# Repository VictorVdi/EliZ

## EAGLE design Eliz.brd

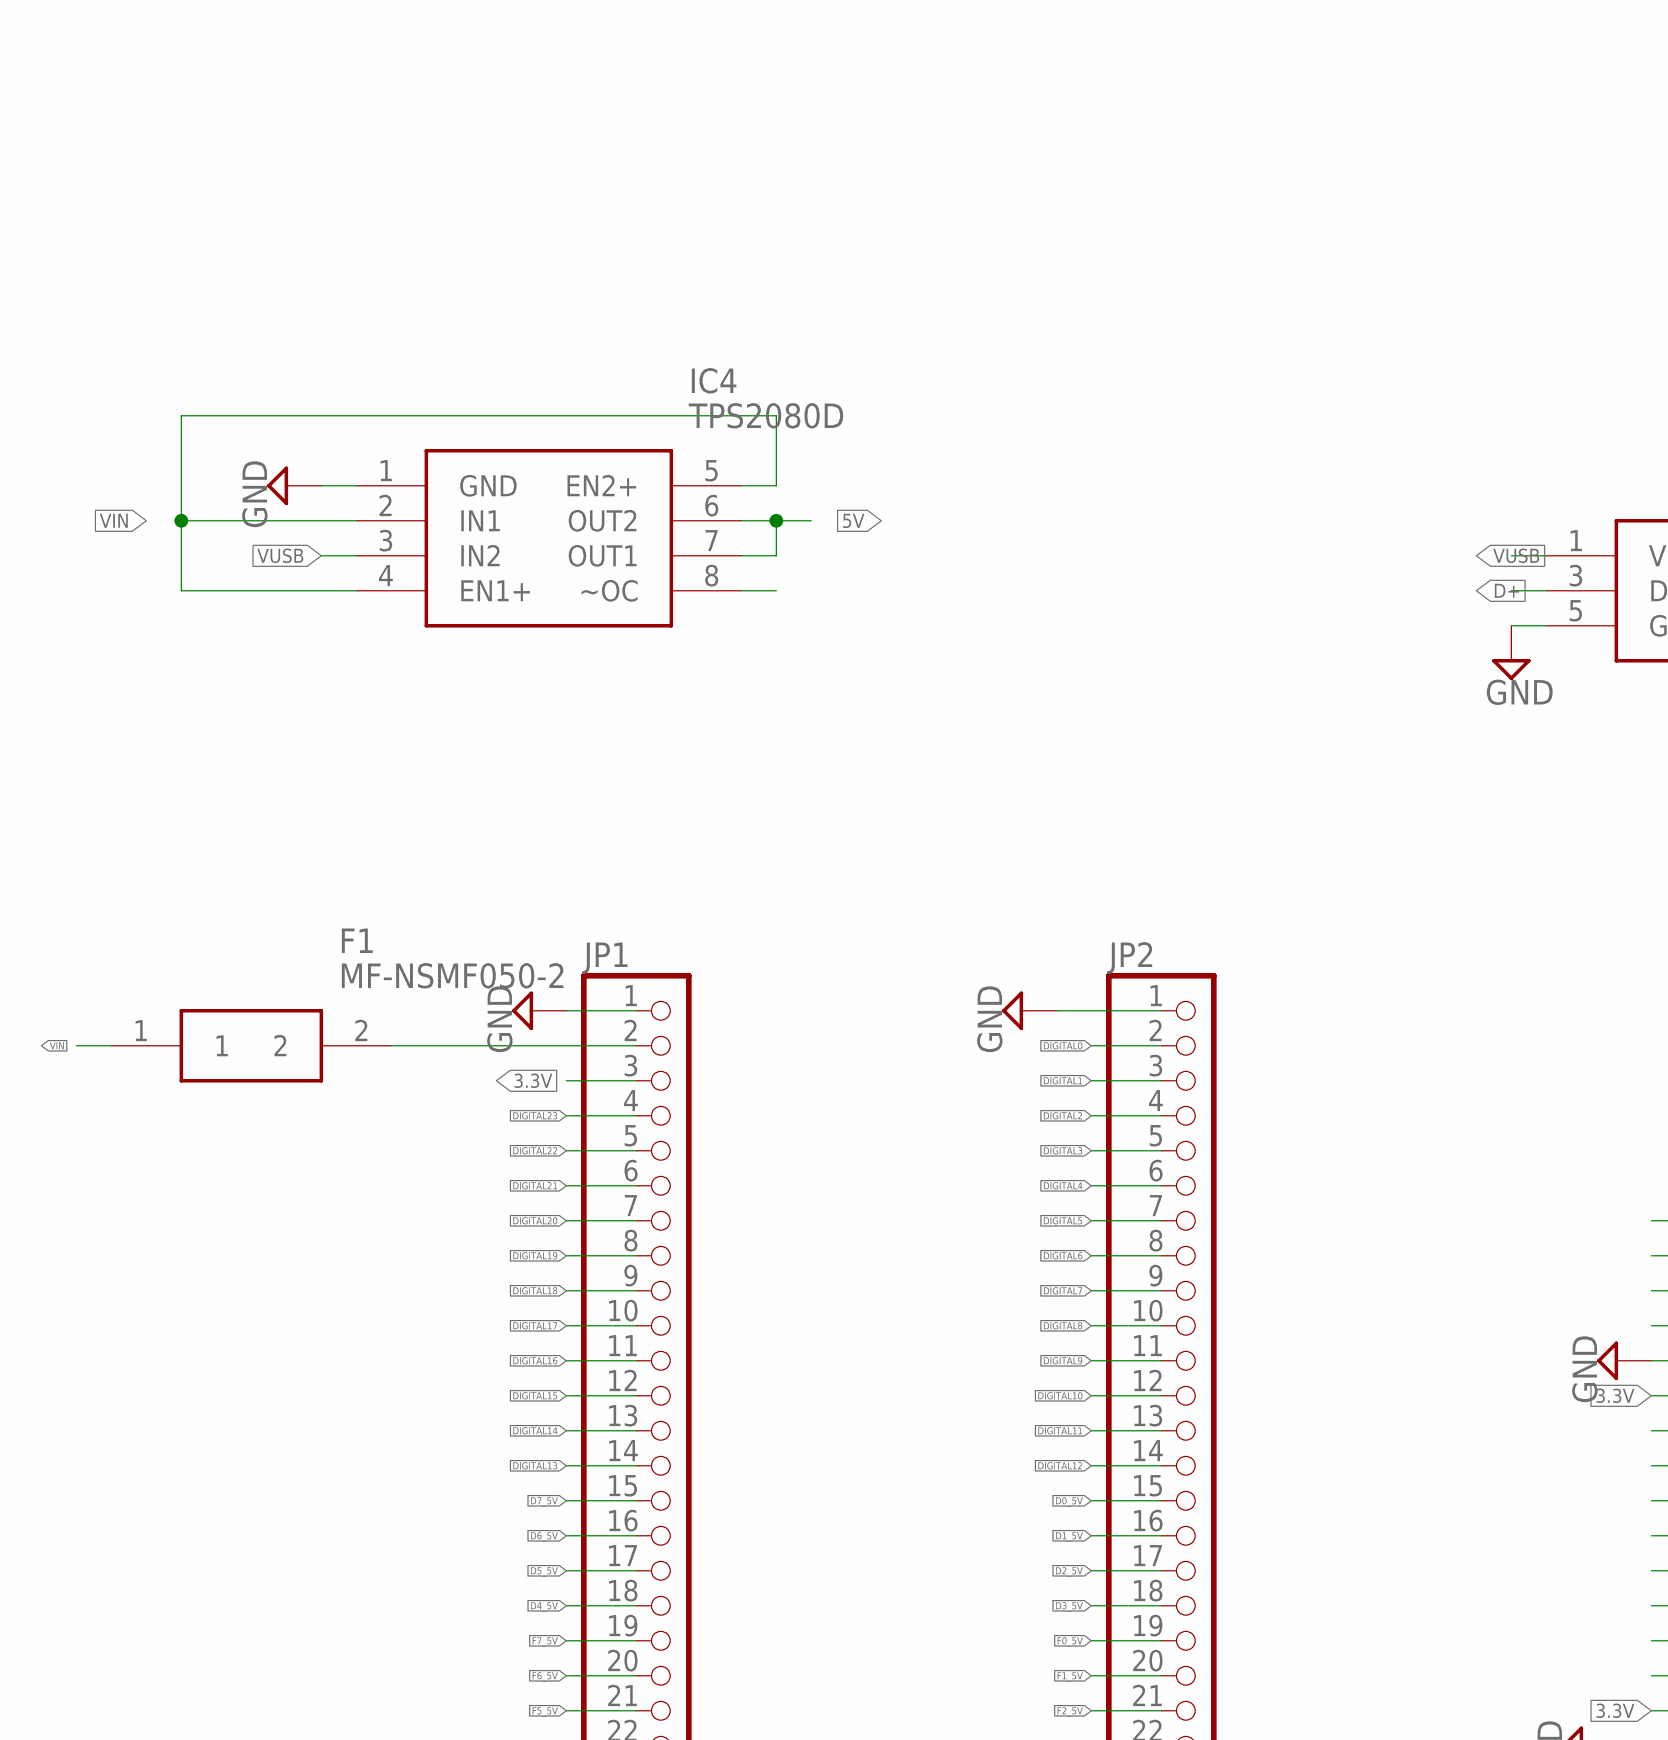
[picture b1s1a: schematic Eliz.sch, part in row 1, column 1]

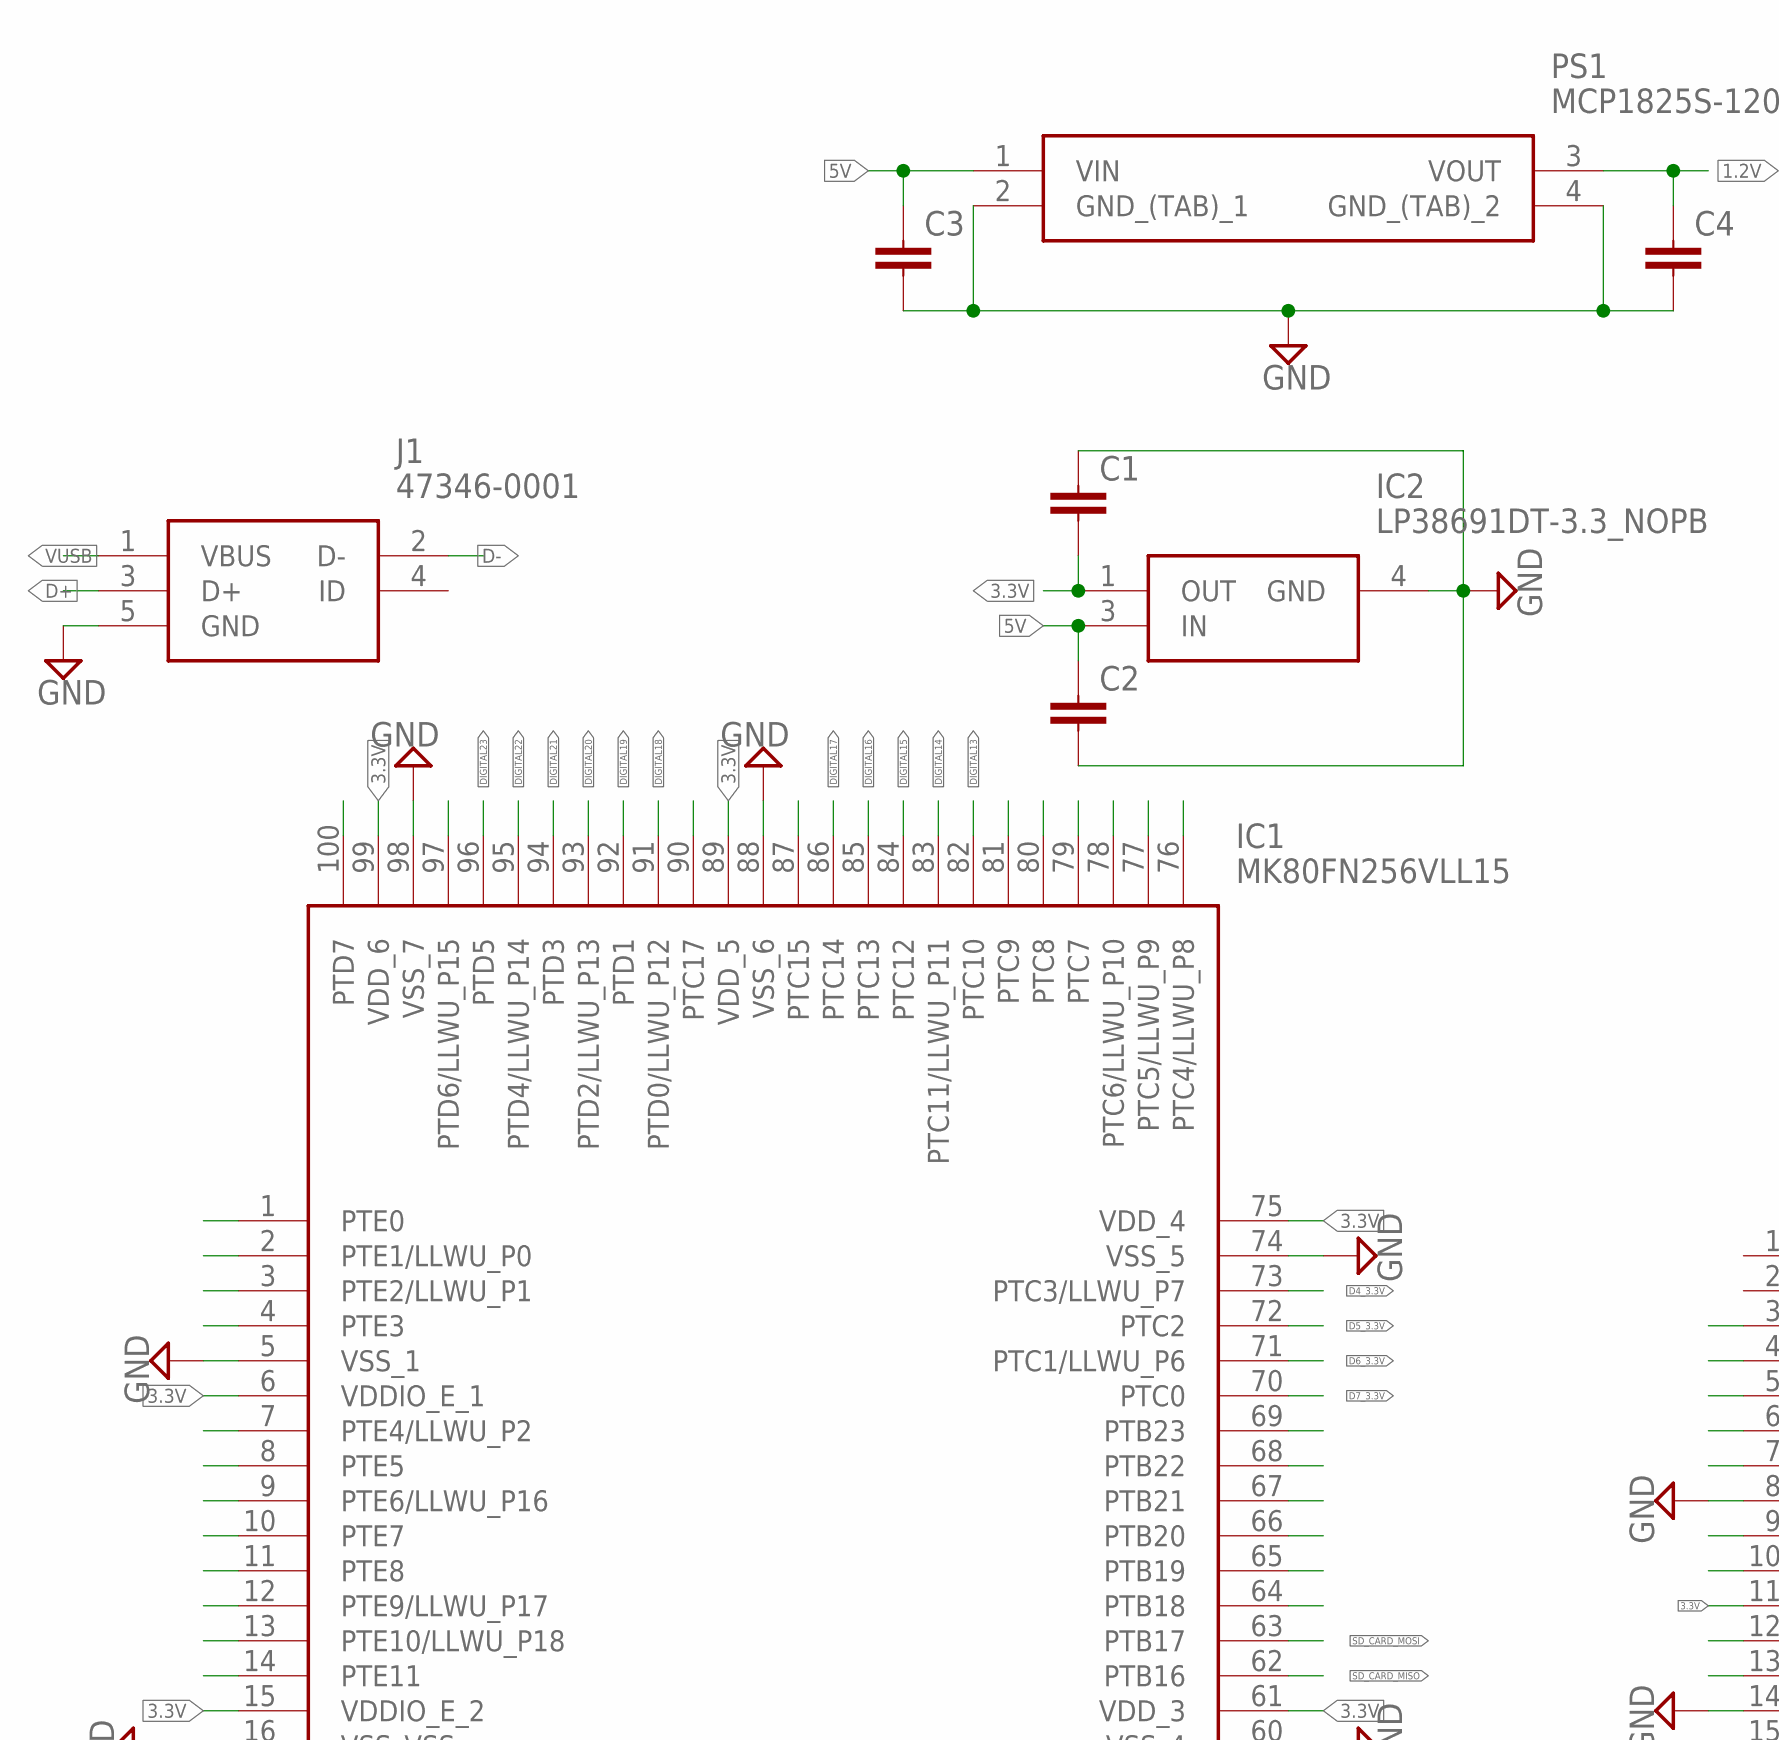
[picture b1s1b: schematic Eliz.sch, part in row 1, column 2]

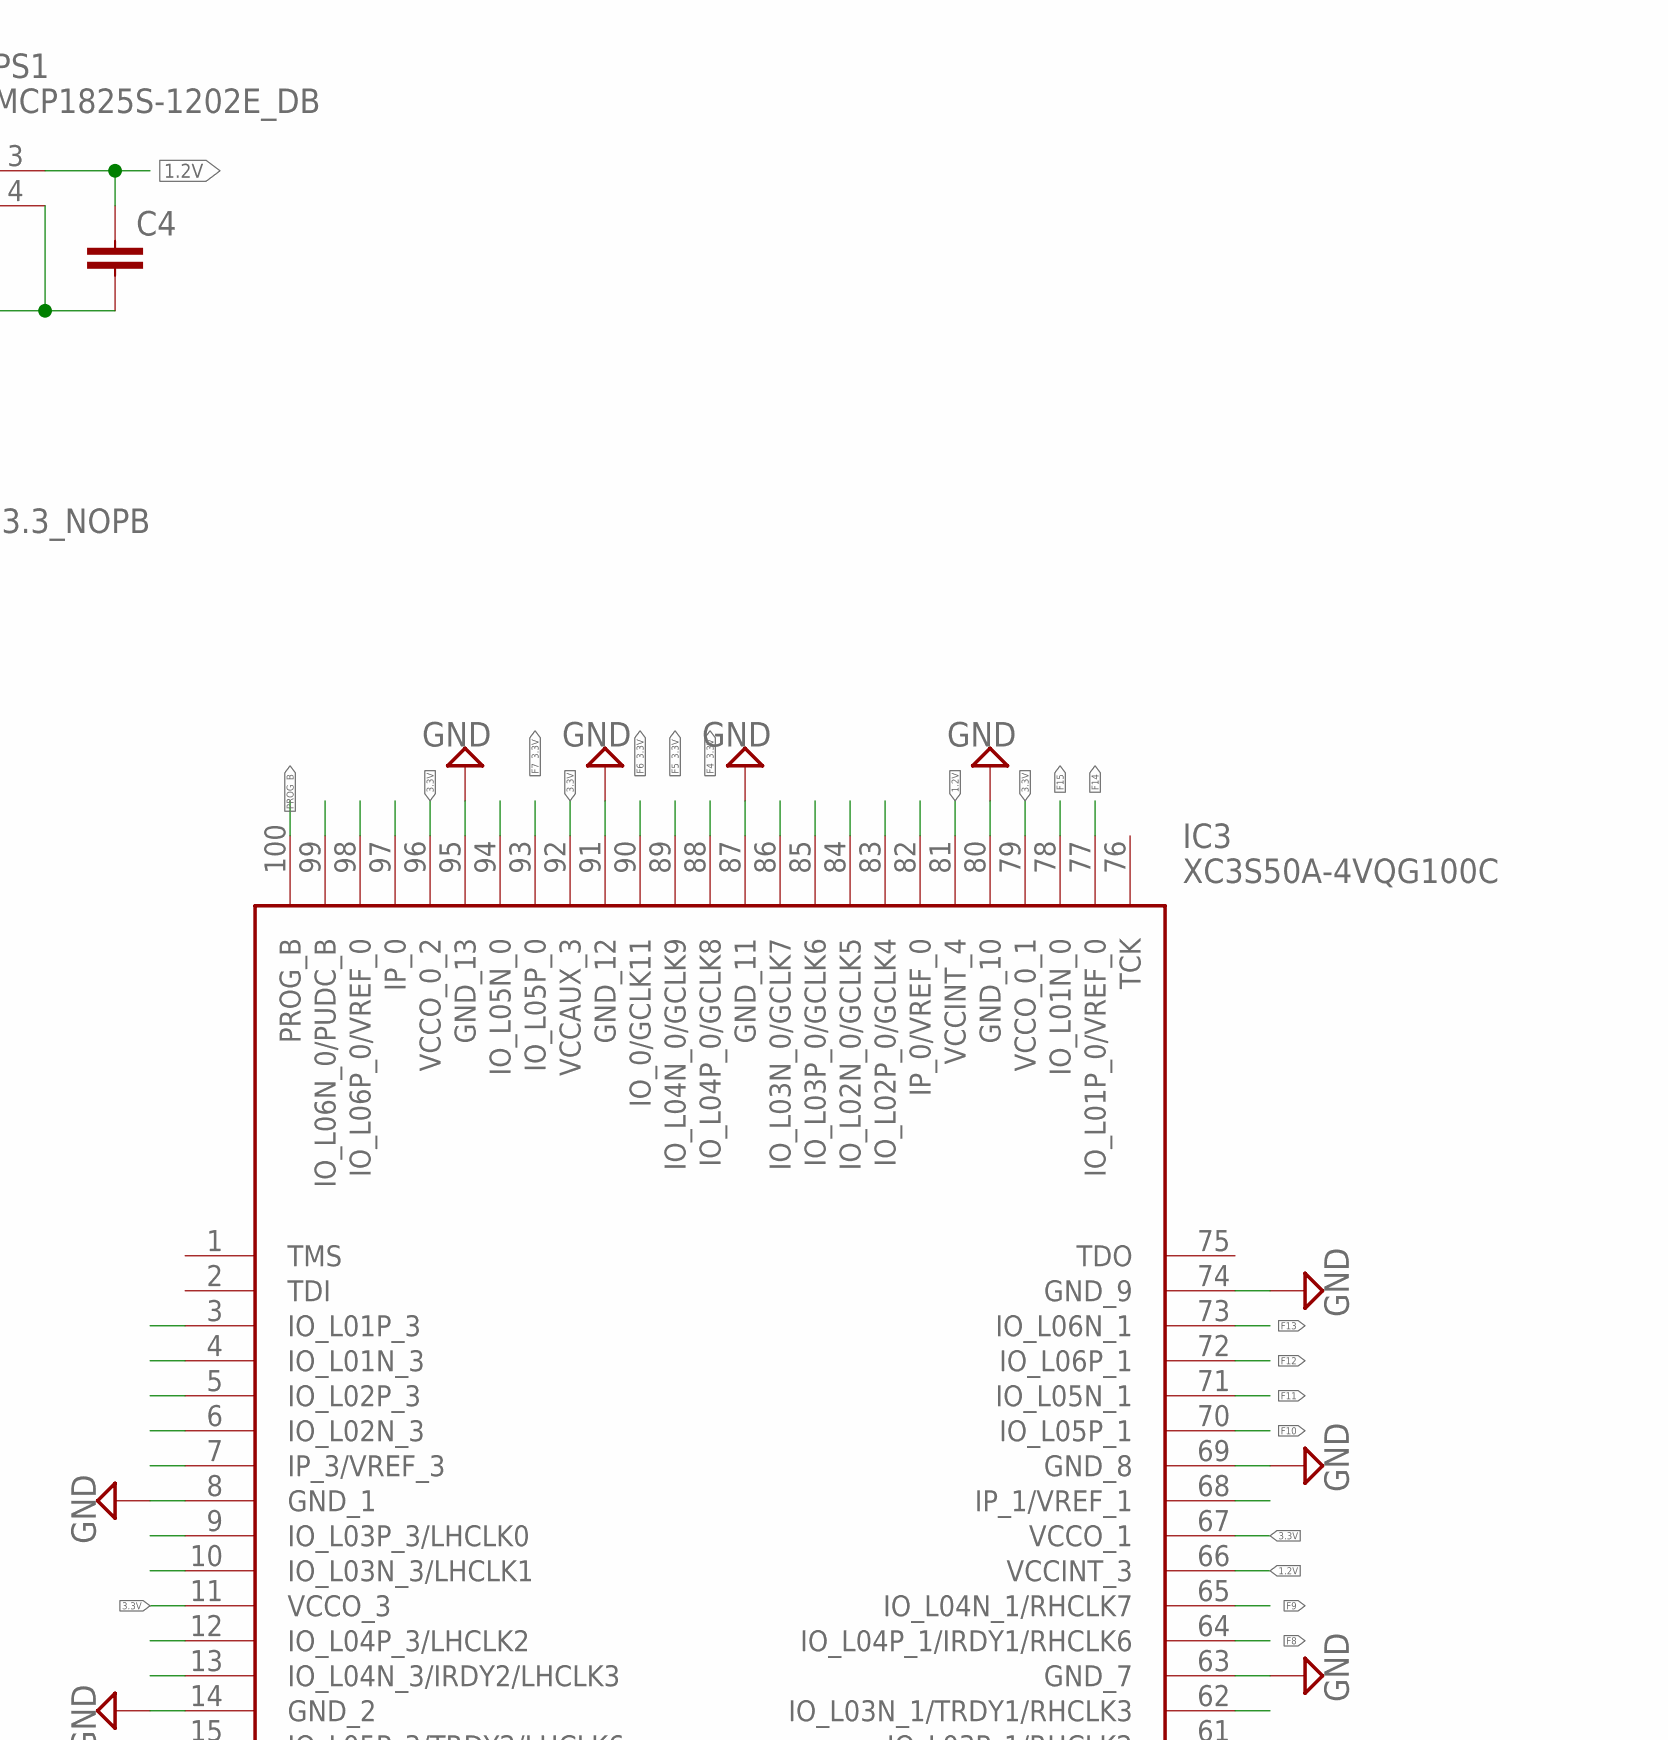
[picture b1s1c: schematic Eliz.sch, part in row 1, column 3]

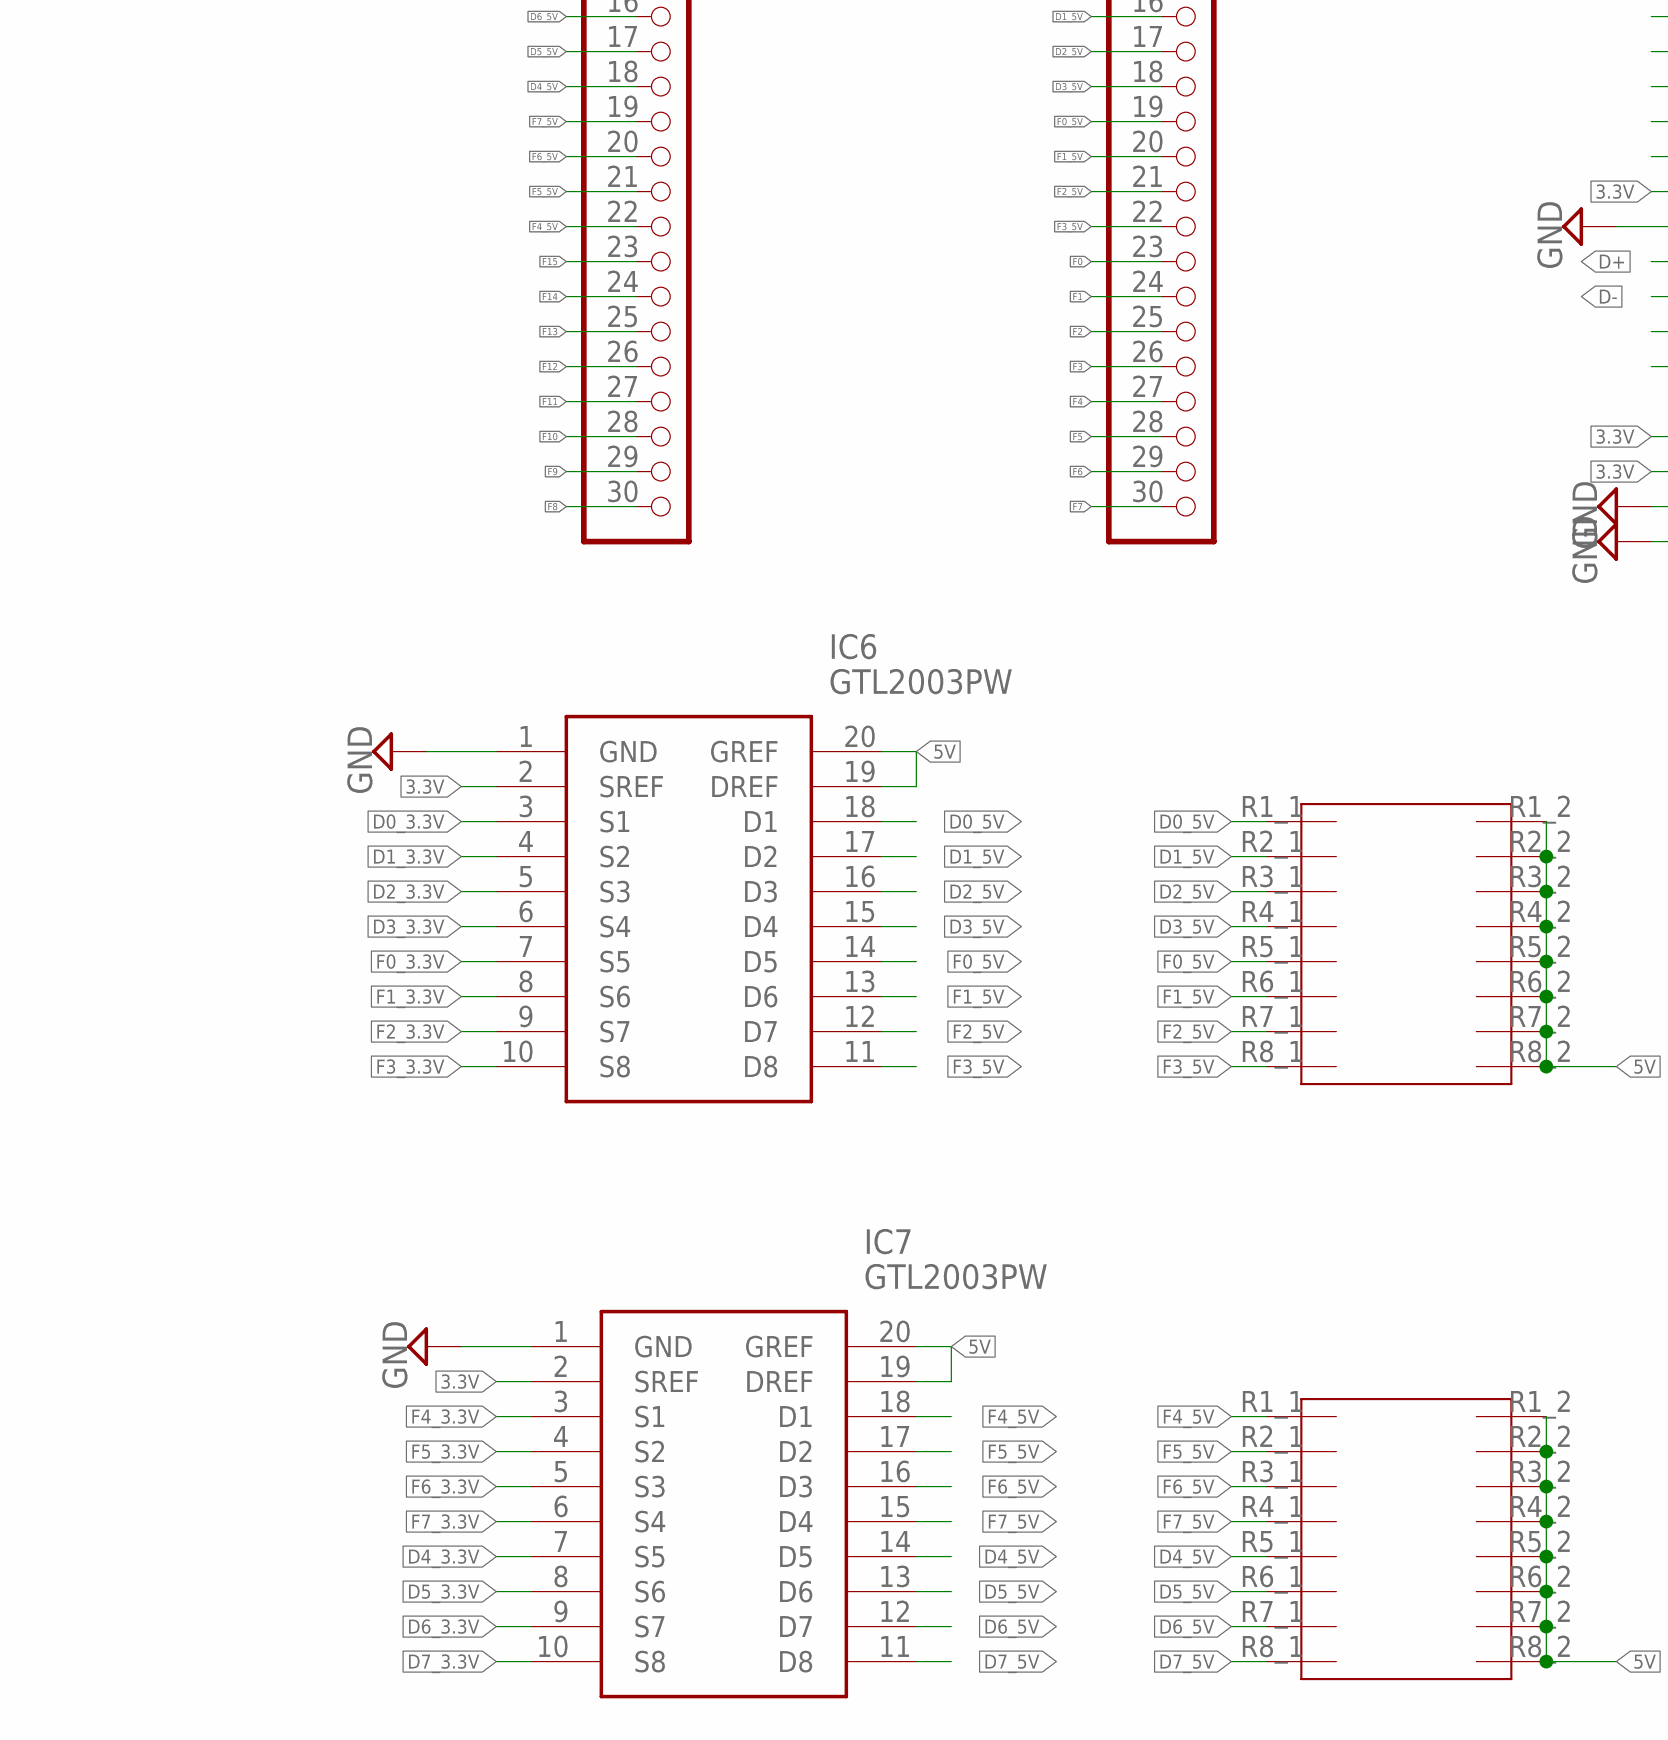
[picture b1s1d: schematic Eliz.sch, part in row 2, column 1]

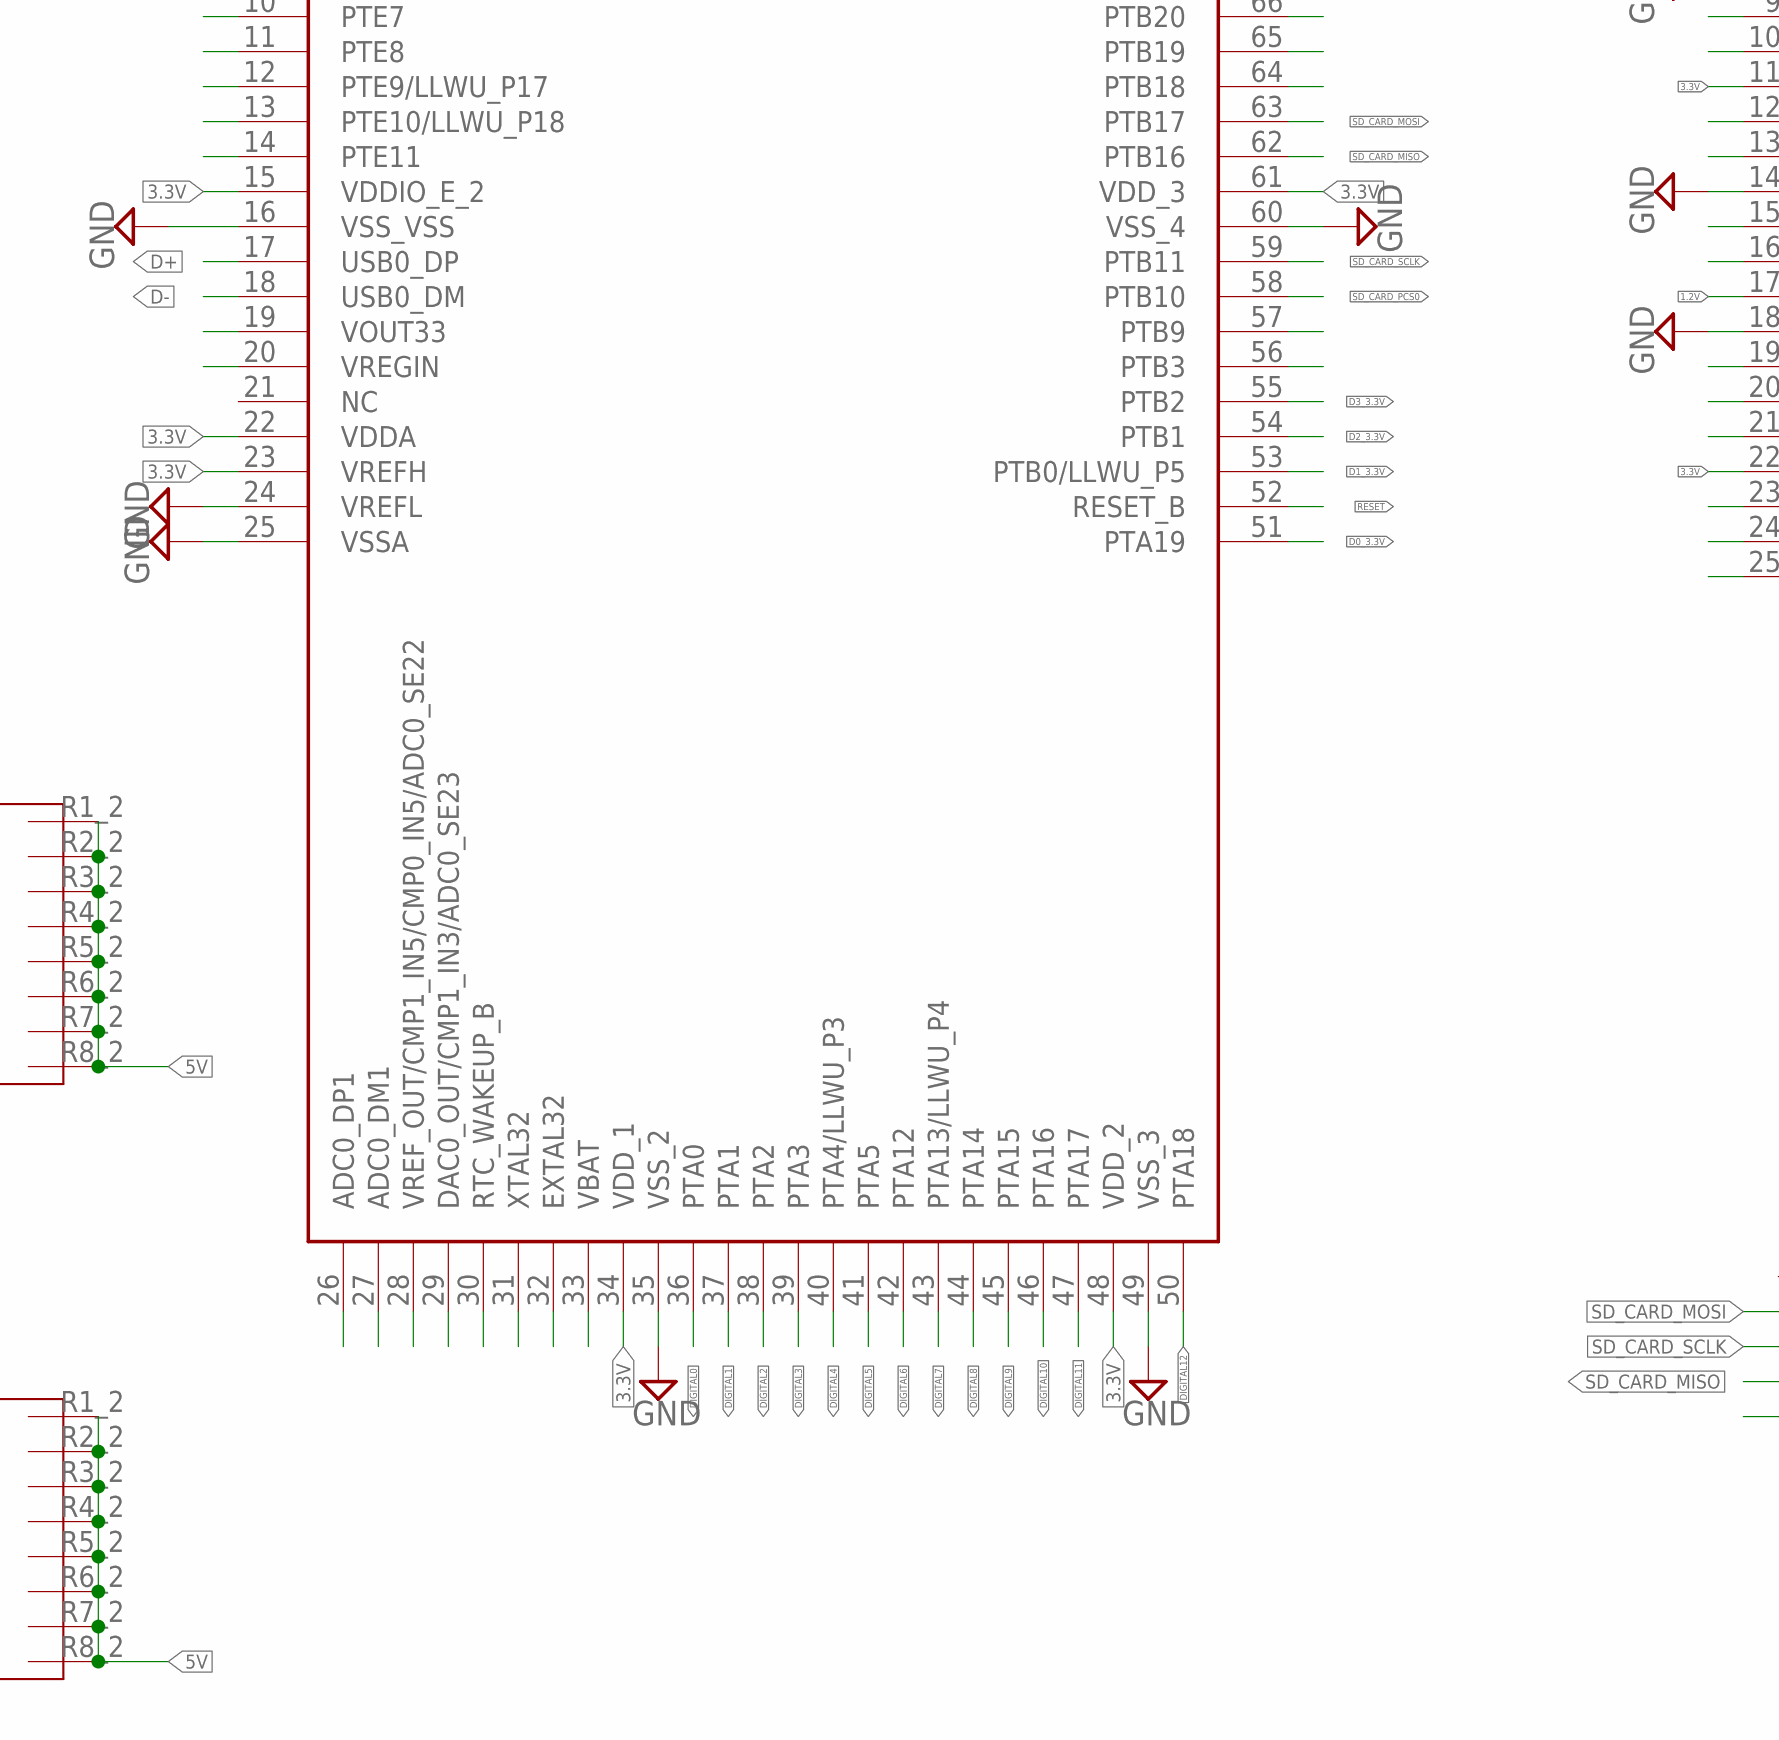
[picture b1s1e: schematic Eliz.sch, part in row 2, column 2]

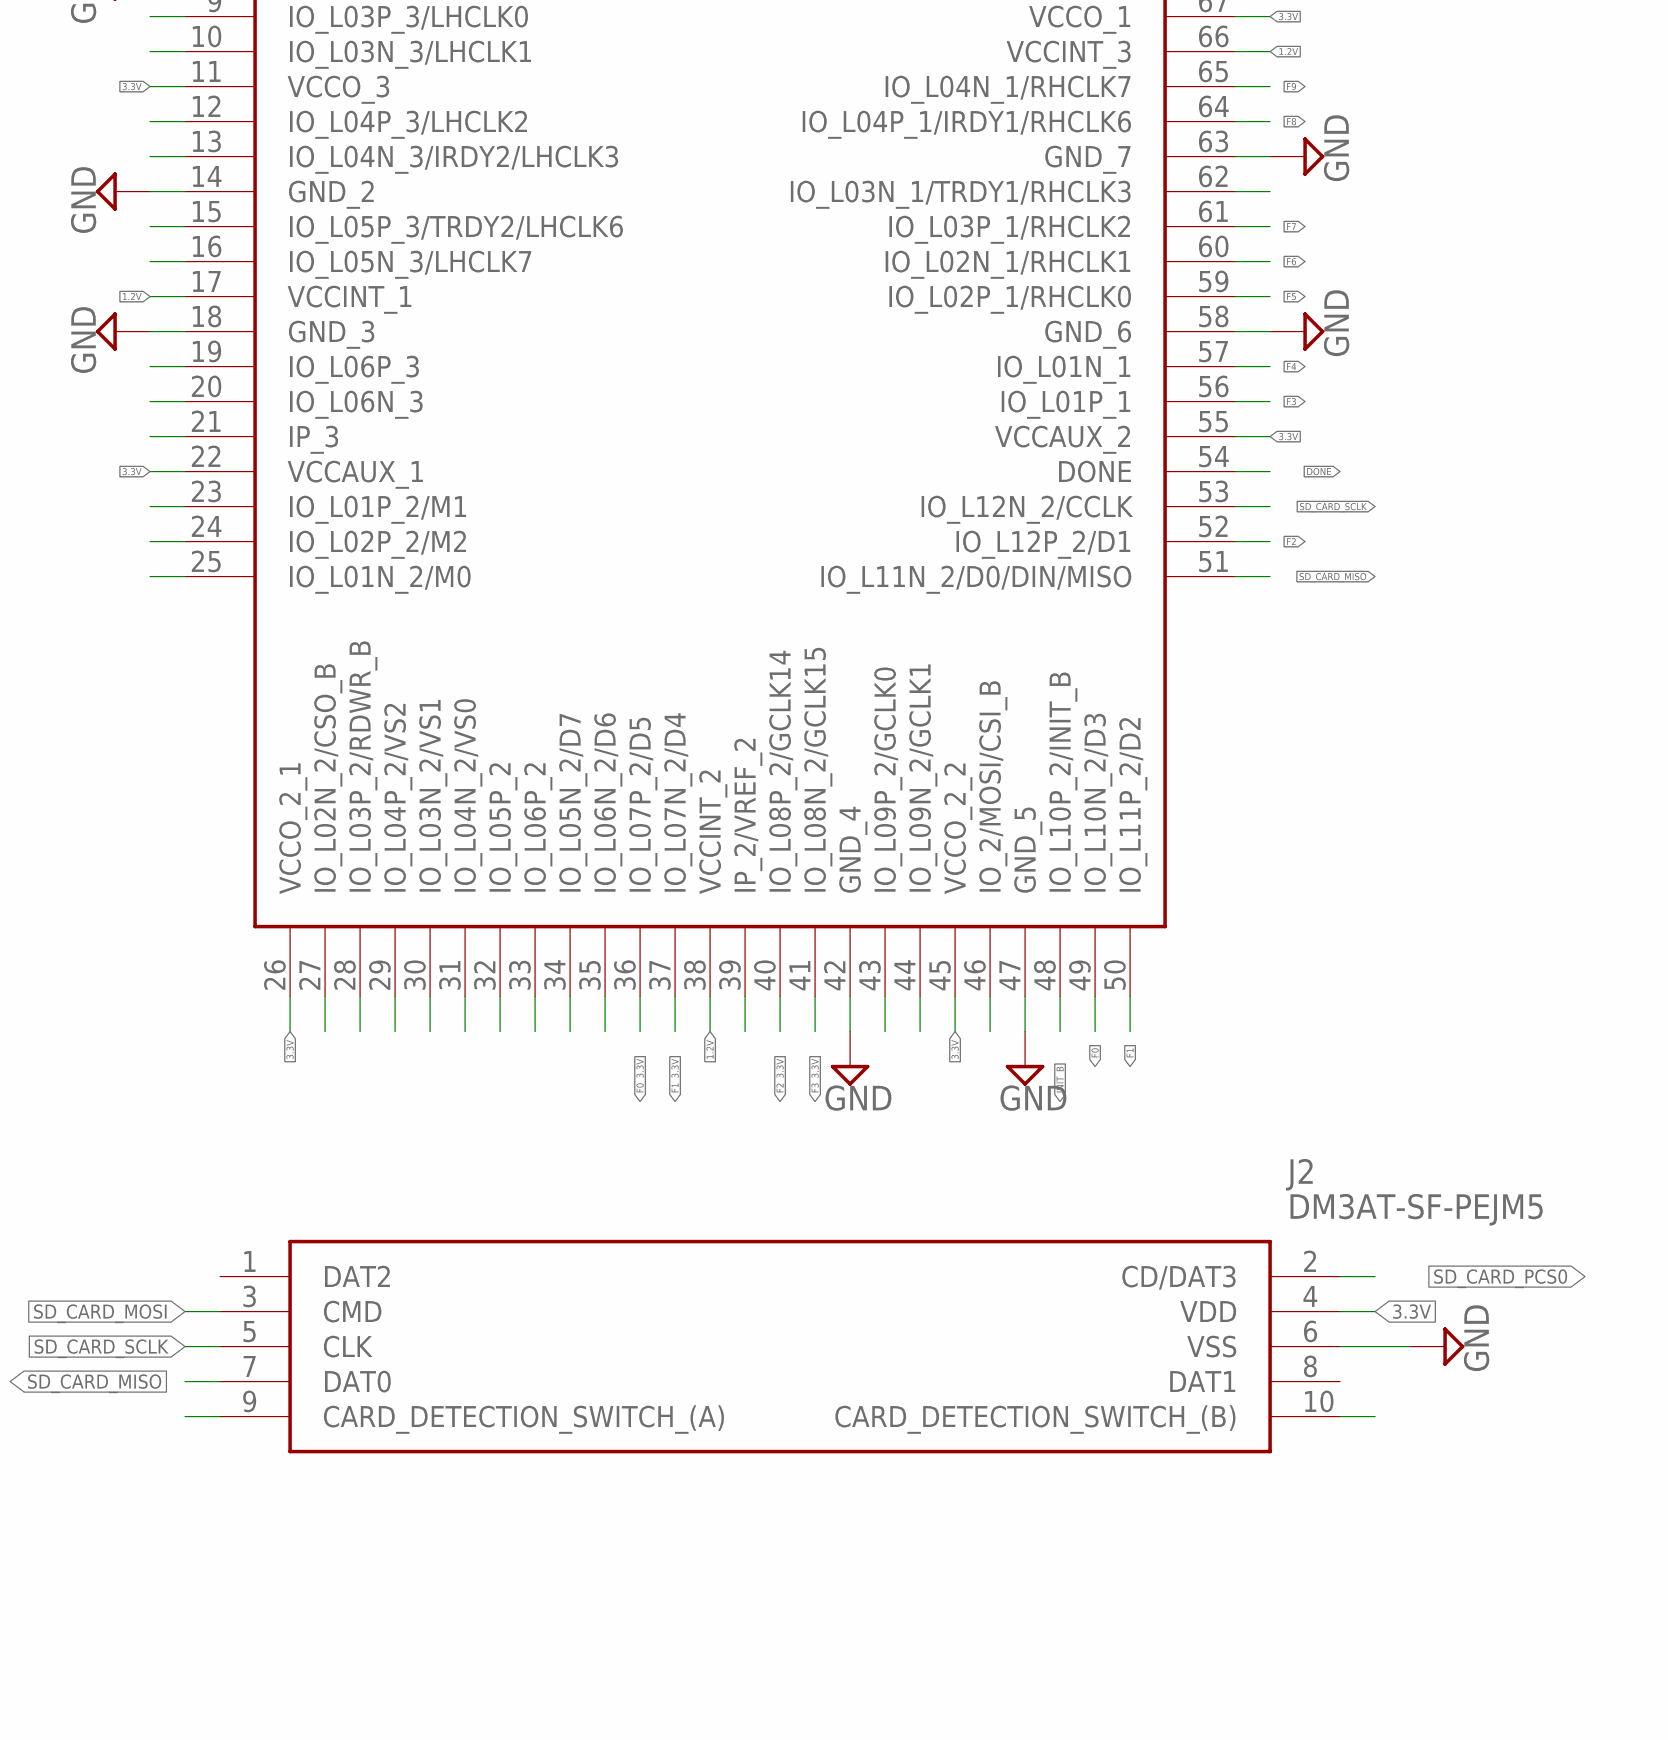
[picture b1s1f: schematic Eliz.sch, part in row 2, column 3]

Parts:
C1, C2, C3, C4: C-EUC0805; C0805
F1: MF-NSMF050-2; FUSC3216X85N
IC1: MK80FN256VLL15; QFP50P1600X1600X170-100N
IC2: LP38691DT-3.3_NOPB; TO228P991X238-3N
IC3: XC3S50A-4VQG100C; QFP50P1600X1600X120-100N
IC4: TPS2080D; SOIC127P600X175-8N
IC6, IC7: GTL2003PW; SOP65P640X110-20N
J1: 47346-0001
J2: DM3AT-SF-PEJM5; DM3AT-SF-PEJM5_1
JP1, JP2: PINHD-1X30; 1X30
PS1: MCP1825S-1202E_DB; SOT230P700X180-4N
U$1, U$2: EXB2HV472JV; 8*4,7KOHM

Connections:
1.2V: C4.1, IC3.17 (VCCINT_1), IC3.38 (VCCINT_2), IC3.66 (VCCINT_3), IC3.81 (VCCINT_4), PS1.3 (VOUT)
3.3V: C1.2, IC1.6 (VDDIO_E_1), IC1.15 (VDDIO_E_2), IC1.22 (VDDA), IC1.23 (VREFH), IC1.34 (VDD_1), IC1.48 (VDD_2), IC1.61 (VDD_3), IC1.75 (VDD_4), IC1.89 (VDD_5), IC1.99 (VDD_6), IC2.1 (OUT), IC3.11 (VCCO_3), IC3.22 (VCCAUX_1), IC3.26 (VCCO_2_1), IC3.45 (VCCO_2_2), IC3.55 (VCCAUX_2), IC3.67 (VCCO_1), IC3.79 (VCCO_0_1), IC3.92 (VCCAUX_3), IC3.96 (VCCO_0_2), IC6.2 (SREF), IC7.2 (SREF), J2.4 (VDD), JP1.3
5V: C2.1, C3.1, IC2.3 (IN), IC4.6 (OUT2), IC4.7 (OUT1), IC6.19 (DREF), IC6.20 (GREF), IC7.19 (DREF), IC7.20 (GREF), PS1.1 (VIN), U$1.R1_2, U$1.R2_2, U$1.R3_2, U$1.R4_2, U$1.R5_2, U$1.R6_2, U$1.R7_2, U$1.R8_2, U$2.R1_2, U$2.R2_2, U$2.R3_2, U$2.R4_2, U$2.R5_2, U$2.R6_2, U$2.R7_2, U$2.R8_2
D0_3.3V: IC1.51 (PTA19), IC6.3 (S1)
D0_5V: IC6.18 (D1), JP2.15, U$1.R1_1
D1_3.3V: IC1.53 (PTB0/LLWU_P5), IC6.4 (S2)
D1_5V: IC6.17 (D2), JP2.16, U$1.R2_1
D2_3.3V: IC1.54 (PTB1), IC6.5 (S3)
D2_5V: IC6.16 (D3), JP2.17, U$1.R3_1
D3_3.3V: IC1.55 (PTB2), IC6.6 (S4)
D3_5V: IC6.15 (D4), JP2.18, U$1.R4_1
D4_3.3V: IC1.73 (PTC3/LLWU_P7), IC7.7 (S5)
D4_5V: IC7.14 (D5), JP1.18, U$2.R5_1
D5_3.3V: IC1.72 (PTC2), IC7.8 (S6)
D5_5V: IC7.13 (D6), JP1.17, U$2.R6_1
D6_3.3V: IC1.71 (PTC1/LLWU_P6), IC7.9 (S7)
D6_5V: IC7.12 (D7), JP1.16, U$2.R7_1
D7_3.3V: IC1.70 (PTC0), IC7.10 (S8)
D7_5V: IC7.11 (D8), JP1.15, U$2.R8_1
D+: IC1.17 (USB0_DP), J1.3 (D+)
D-: IC1.18 (USB0_DM), J1.2 (D-)
DIGITAL0: IC1.36 (PTA0), JP2.2
DIGITAL1: IC1.37 (PTA1), JP2.3
DIGITAL2: IC1.38 (PTA2), JP2.4
DIGITAL3: IC1.39 (PTA3), JP2.5
DIGITAL4: IC1.40 (PTA4/LLWU_P3), JP2.6
DIGITAL5: IC1.41 (PTA5), JP2.7
DIGITAL6: IC1.42 (PTA12), JP2.8
DIGITAL7: IC1.43 (PTA13/LLWU_P4), JP2.9
DIGITAL8: IC1.44 (PTA14), JP2.10
DIGITAL9: IC1.45 (PTA15), JP2.11
DIGITAL10: IC1.46 (PTA16), JP2.12
DIGITAL11: IC1.47 (PTA17), JP2.13
DIGITAL12: IC1.50 (PTA18), JP2.14
DIGITAL13: IC1.82 (PTC10), JP1.14
DIGITAL14: IC1.83 (PTC11/LLWU_P11), JP1.13
DIGITAL15: IC1.84 (PTC12), JP1.12
DIGITAL16: IC1.85 (PTC13), JP1.11
DIGITAL17: IC1.86 (PTC14), JP1.10
DIGITAL18: IC1.91 (PTD0/LLWU_P12), JP1.9
DIGITAL19: IC1.92 (PTD1), JP1.8
DIGITAL20: IC1.93 (PTD2/LLWU_P13), JP1.7
DIGITAL21: IC1.94 (PTD3), JP1.6
DIGITAL22: IC1.95 (PTD4/LLWU_P14), JP1.5
DIGITAL23: IC1.96 (PTD5), JP1.4
DONE: IC3.54 (DONE)
F0: IC3.49 (IO_L10N_2/D3), JP2.23
F0_3.3V: IC3.36 (IO_L07P_2/D5), IC6.7 (S5)
F0_5V: IC6.14 (D5), JP2.19, U$1.R5_1
F1: IC3.50 (IO_L11P_2/D2), JP2.24
F1_3.3V: IC3.37 (IO_L07N_2/D4), IC6.8 (S6)
F1_5V: IC6.13 (D6), JP2.20, U$1.R6_1
F2: IC3.52 (IO_L12P_2/D1), JP2.25
F2_3.3V: IC3.40 (IO_L08P_2/GCLK14), IC6.9 (S7)
F2_5V: IC6.12 (D7), JP2.21, U$1.R7_1
F3: IC3.56 (IO_L01P_1), JP2.26
F3_3.3V: IC3.41 (IO_L08N_2/GCLK15), IC6.10 (S8)
F3_5V: IC6.11 (D8), JP2.22, U$1.R8_1
F4: IC3.57 (IO_L01N_1), JP2.27
F4_3.3V: IC3.88 (IO_L04P_0/GCLK8), IC7.3 (S1)
F4_5V: IC7.18 (D1), JP1.22, U$2.R1_1
F5: IC3.59 (IO_L02P_1/RHCLK0), JP2.28
F5_3.3V: IC3.89 (IO_L04N_0/GCLK9), IC7.4 (S2)
F5_5V: IC7.17 (D2), JP1.21, U$2.R2_1
F6: IC3.60 (IO_L02N_1/RHCLK1), JP2.29
F6_3.3V: IC3.90 (IO_0/GCLK11), IC7.5 (S3)
F6_5V: IC7.16 (D3), JP1.20, U$2.R3_1
F7: IC3.61 (IO_L03P_1/RHCLK2), JP2.30
F7_3.3V: IC3.93 (IO_L05P_0), IC7.6 (S4)
F7_5V: IC7.15 (D4), JP1.19, U$2.R4_1
F8: IC3.64 (IO_L04P_1/IRDY1/RHCLK6), JP1.30
F9: IC3.65 (IO_L04N_1/RHCLK7), JP1.29
F10: IC3.70 (IO_L05P_1), JP1.28
F11: IC3.71 (IO_L05N_1), JP1.27
F12: IC3.72 (IO_L06P_1), JP1.26
F13: IC3.73 (IO_L06N_1), JP1.25
F14: IC3.77 (IO_L01P_0/VREF_0), JP1.24
F15: IC3.78 (IO_L01N_0), JP1.23
GND: C1.1, C2.2, C3.2, C4.2, IC1.5 (VSS_1), IC1.16 (VSS_VSS), IC1.24 (VREFL), IC1.25 (VSSA), IC1.35 (VSS_2), IC1.49 (VSS_3), IC1.60 (VSS_4), IC1.74 (VSS_5), IC1.88 (VSS_6), IC1.98 (VSS_7), IC2.4 (GND), IC3.8 (GND_1), IC3.14 (GND_2), IC3.18 (GND_3), IC3.42 (GND_4), IC3.47 (GND_5), IC3.58 (GND_6), IC3.63 (GND_7), IC3.69 (GND_8), IC3.74 (GND_9), IC3.80 (GND_10), IC3.87 (GND_11), IC3.91 (GND_12), IC3.95 (GND_13), IC4.1 (GND), IC6.1 (GND), IC7.1 (GND), J1.5 (GND), J2.6 (VSS), JP1.1, JP2.1, PS1.2 (GND_(TAB)_1), PS1.4 (GND_(TAB)_2)
INIT_B: IC3.48 (IO_L10P_2/INIT_B)
unnamed: F1.2, JP1.2
PROG_B: IC3.100 (PROG_B)
RESET: IC1.52 (RESET_B)
SD_CARD_MISO: IC1.62 (PTB16), IC3.51 (IO_L11N_2/D0/DIN/MISO), J2.7 (DAT0)
SD_CARD_MOSI: IC1.63 (PTB17), J2.3 (CMD)
SD_CARD_PCS0: IC1.58 (PTB10), J2.2 (CD/DAT3)
SD_CARD_SCLK: IC1.59 (PTB11), IC3.53 (IO_L12N_2/CCLK), J2.5 (CLK)
VIN: F1.1, IC4.2 (IN1), IC4.4 (EN1+), IC4.5 (EN2+)
VUSB: IC4.3 (IN2), J1.1 (VBUS)

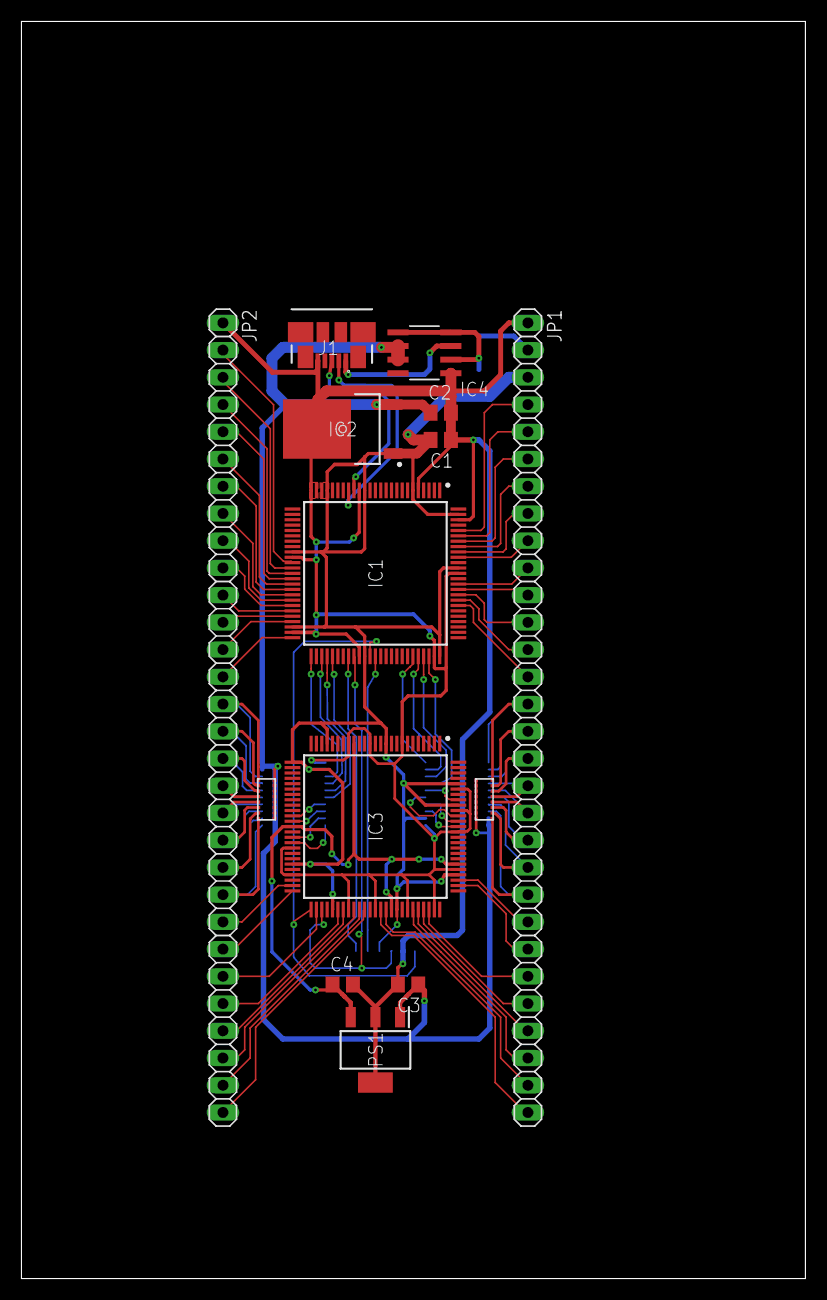
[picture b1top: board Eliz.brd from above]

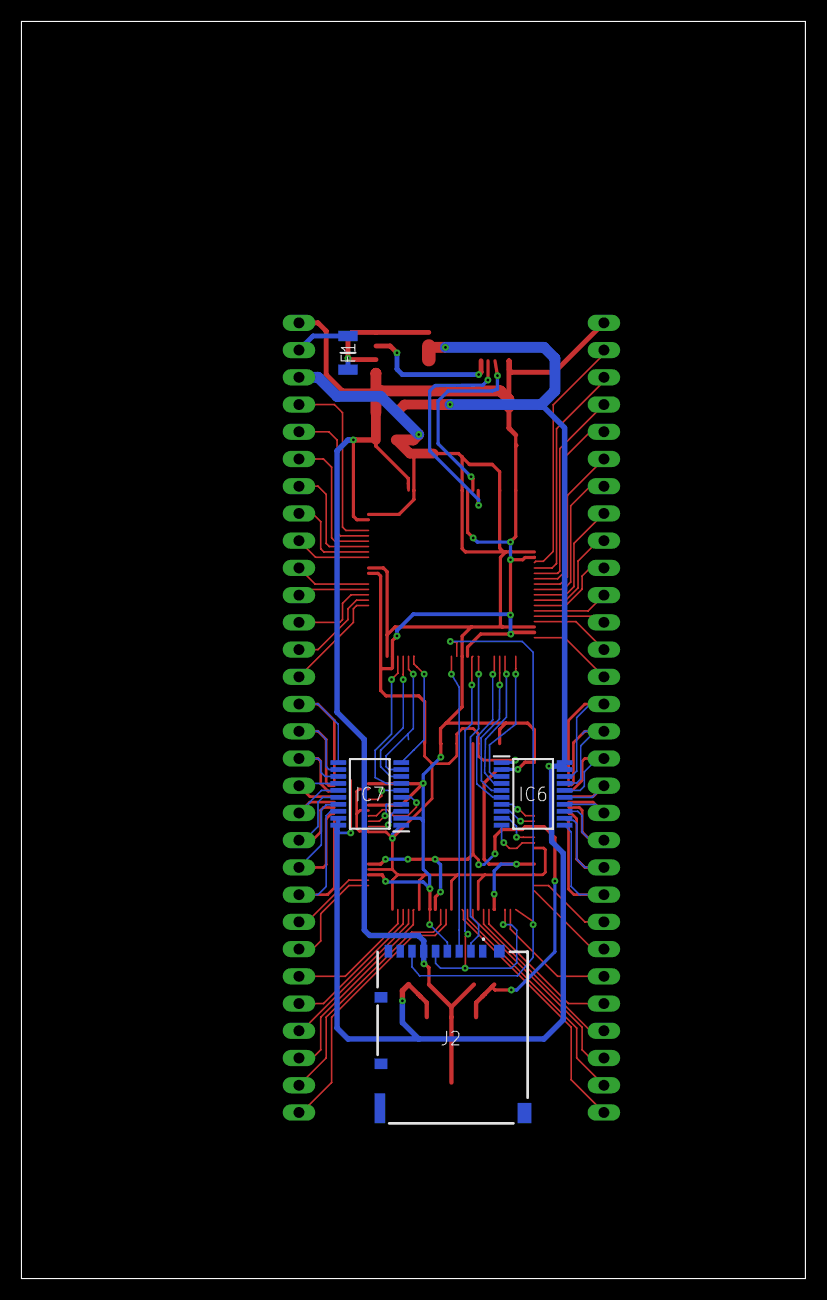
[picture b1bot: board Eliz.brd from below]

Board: 2 copper layers, 73.1 x 117.3 mm, 18 parts (4 on the bottom side), 85 nets.

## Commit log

2018-10-06 Projet presque fini
